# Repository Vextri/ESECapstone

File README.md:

# Capstone
Repo for ESE Capstone

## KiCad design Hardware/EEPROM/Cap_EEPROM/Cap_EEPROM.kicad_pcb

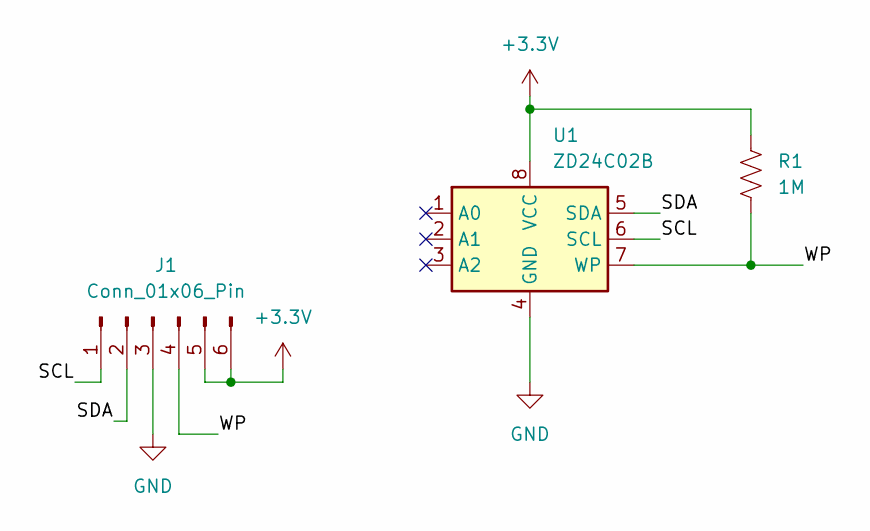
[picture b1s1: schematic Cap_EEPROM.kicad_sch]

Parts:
J1: Conn_01x06_Pin; EEPROM_Board_Pads
R1: 1M; R_0402_1005Metric_Pad0.72x0.64mm_HandSolder
U1: ZD24C02B; DFN-8-1EP_3x2mm_P0.5mm_EP1.3x1.5mm

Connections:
+3.3V: J1.5, J1.6, R1.1, U1.8 (VCC)
/SCL: J1.1, U1.6 (SCL)
/SDA: J1.2, U1.5 (SDA)
/WP: J1.4, R1.2, U1.7 (WP)
GND: J1.3, U1.4 (GND), U1.9 (GND)

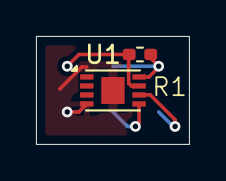
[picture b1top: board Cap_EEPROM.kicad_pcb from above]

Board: 2 copper layers, 8.5 x 6.0 mm, 3 parts (1 on the bottom side), 5 nets.

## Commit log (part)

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2026-03-26 Our First Commit....technically. This is the sumamtion of all the work done as of March 26th 2026. This includes the ProtoPill Enclosure, MCU code, and the preliminary Altium Design files (No longer 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
2026-03-28 saving our protopillv1 print
2026-03-30 made changes to mechanical design and started esp code setup
2026-03-31 saving code from dispensing logic pre test as complete system
2026-03-31 saving progress
2026-04-01 Updated Platform on the Revision 3 file
2026-04-01 Updated Platform model file and saved as 4th revision
2026-04-02 updating dispensing code
2026-04-02 updating
2026-04-02 saving the changes to container and container1
2026-04-03 updated esp code
2026-04-05 added a small sizing for motor holder (literally nothing) and updated the mikenike rotater for deeper holes for the magnet
2026-04-06 current documentation
2026-04-06 updated esp code for live dispense and updating retry logic on rpi pico
2026-04-07 saving
2026-04-07 this is updating the code to behave more like the final system, added real ui interaction and timing, edge cases are needing to be adressed in future iterations
2026-04-08 modified protopill (V5)
2026-04-08 idk but im printing
2026-04-09 mech
2026-04-14 saving work
2026-04-18 rolledback, this was code used for demo presentation
2026-05-12 Started expanding design for full product enclosure
2026-05-21 pillStation creation
2026-05-21 saving code screen + slight mcu changes
2026-06-05 updated code for steppers and screen
2026-06-09 V1 of pillstation errors in design, screen cutout, missing final ventalation, piezo cutouts, and final board holder
2026-06-16 updating before tech assess 1, includes screen + audio + bug fixes
